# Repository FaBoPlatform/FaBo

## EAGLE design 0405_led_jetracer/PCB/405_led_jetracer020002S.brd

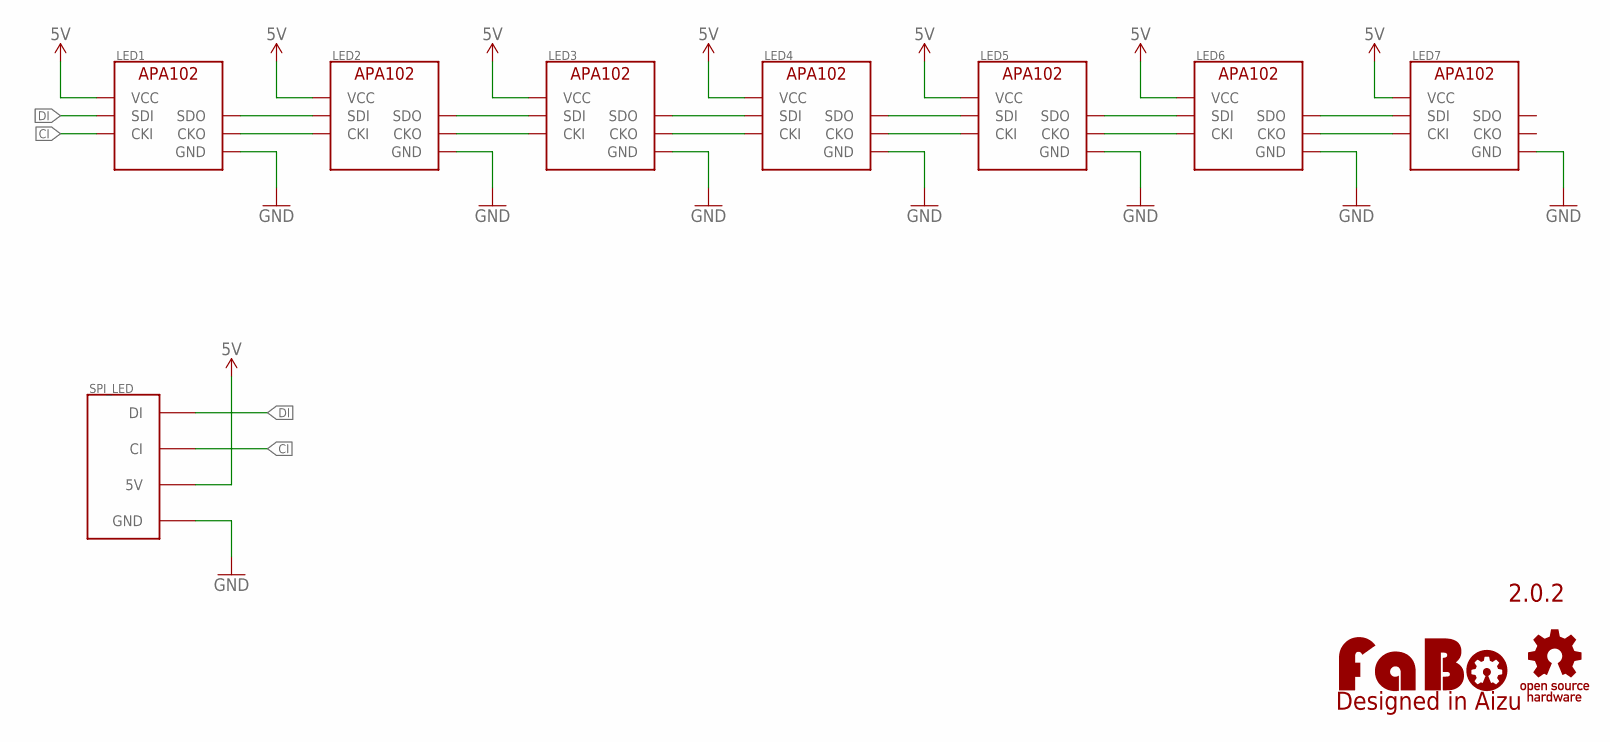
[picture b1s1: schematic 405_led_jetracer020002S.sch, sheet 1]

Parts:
LED1, LED2, LED3, LED4, LED5, LED6, LED7: APA102_IPIXEL; APA102_2020
LOGO1: LOGO_OSHW-S_BOTTOM; LOGO_OSHW_S_BOTTOM
LOGO2: LOGO_FABO-S; LOGO_FABO_S
SPI_LED: SPI-LED; FABO_BRICK_SPI_LED_S04B-PASK-2

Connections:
5V: LED1.VCC, LED2.VCC, LED3.VCC, LED4.VCC, LED5.VCC, LED6.VCC, LED7.VCC, SPI_LED.5V
CI: LED1.CKI, SPI_LED.CI
CI1: LED1.CKO, LED2.CKI
CI2: LED2.CKO, LED3.CKI
CI3: LED3.CKO, LED4.CKI
CI4: LED4.CKO, LED5.CKI
CI5: LED5.CKO, LED6.CKI
DI: LED1.SDI, SPI_LED.DI
DI1: LED1.SDO, LED2.SDI
DI2: LED2.SDO, LED3.SDI
DI3: LED3.SDO, LED4.SDI
DI4: LED4.SDO, LED5.SDI
DI5: LED5.SDO, LED6.SDI
GND: LED1.GND, LED2.GND, LED3.GND, LED4.GND, LED5.GND, LED6.GND, LED7.GND, SPI_LED.GND
unnamed: LED6.SDO, LED7.SDI
unnamed: LED6.CKO, LED7.CKI

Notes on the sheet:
2.0.2

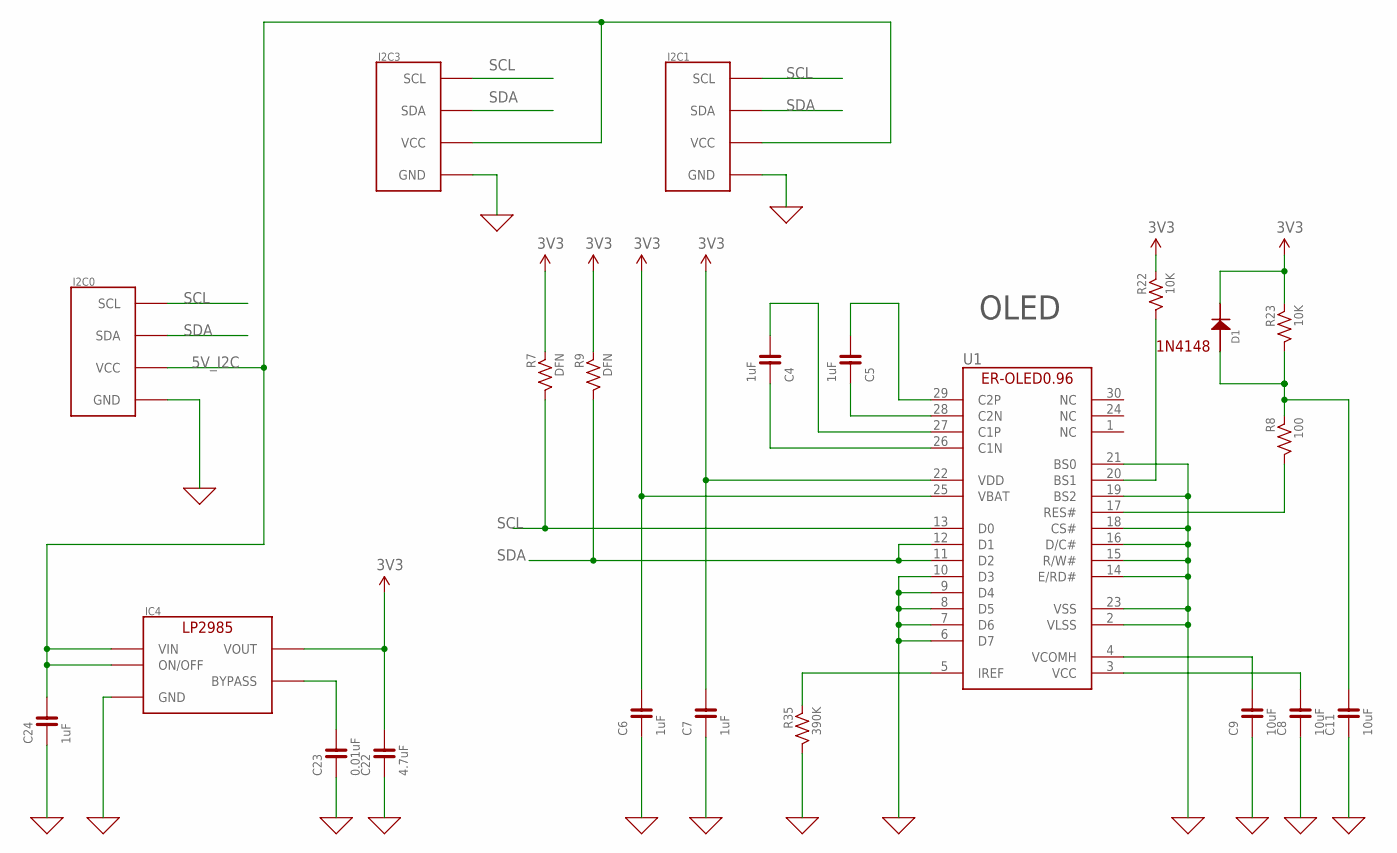
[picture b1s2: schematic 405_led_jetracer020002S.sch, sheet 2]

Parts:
C4, C5, C6, C7, C24: 1uF; 0603
C8, C9, C11: 10uF; 0603
C22: 4.7uF; 0603
C23: 0.01uF; 0603
D1: 1N4148; 1N4148W
I2C0, I2C1, I2C3: FABO_BRICK_I2C-S04B-PASK-2; FABO_BRICK_I2C_S04B-PASK-2
IC4: LP2985-33DBV; SOT-23-5
R7, R9: DFN; 0603
R8: 100; 0603
R22, R23: 10K; 0603
R35: 390K; 0603
U1: ER-OLED0.96-1ER-CON30HT-1; ER-CON30HT-1

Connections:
0: C6.1, C7.1, C8.1, C9.1, C11.1, C22.1, C23.1, C24.1, I2C0.GND, I2C1.GND, I2C3.GND, IC4.2 (GND), R35.2, U1.2 (VLSS), U1.6 (D7), U1.7 (D6), U1.8 (D5), U1.9 (D4), U1.10 (D3), U1.14 (E/RD#), U1.15 (R/W#), U1.16 (D/C#), U1.18 (CS#), U1.19 (BS2), U1.21 (BS0), U1.23 (VSS)
3V3: C6.2, C7.2, C22.2, D1.CATHODE, IC4.5 (VOUT), R7.1, R9.1, R22.1, R23.1, U1.22 (VDD), U1.25 (VBAT)
5V_I2C: C24.2, I2C0.VCC, I2C1.VCC, I2C3.VCC, IC4.1 (VIN), IC4.3 (ON/OFF)
unnamed: C23.2, IC4.4 (BYPASS)
unnamed: C4.2, U1.27 (C1P)
unnamed: C4.1, U1.26 (C1N)
unnamed: C5.1, U1.28 (C2N)
unnamed: C5.2, U1.29 (C2P)
unnamed: R35.1, U1.5 (IREF)
unnamed: C9.2, U1.4 (VCOMH)
unnamed: C8.2, U1.3 (VCC)
unnamed: R8.2, U1.17 (RES#)
unnamed: C11.2, D1.ANODE, R8.1, R23.2
unnamed: R22.2, U1.20 (BS1)
SCL: I2C0.SCL, I2C1.SCL, I2C3.SCL, R7.2, U1.13 (D0)
SDA: I2C0.SDA, I2C1.SDA, I2C3.SDA, R9.2, U1.11 (D2), U1.12 (D1)

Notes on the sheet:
1N4148
OLED

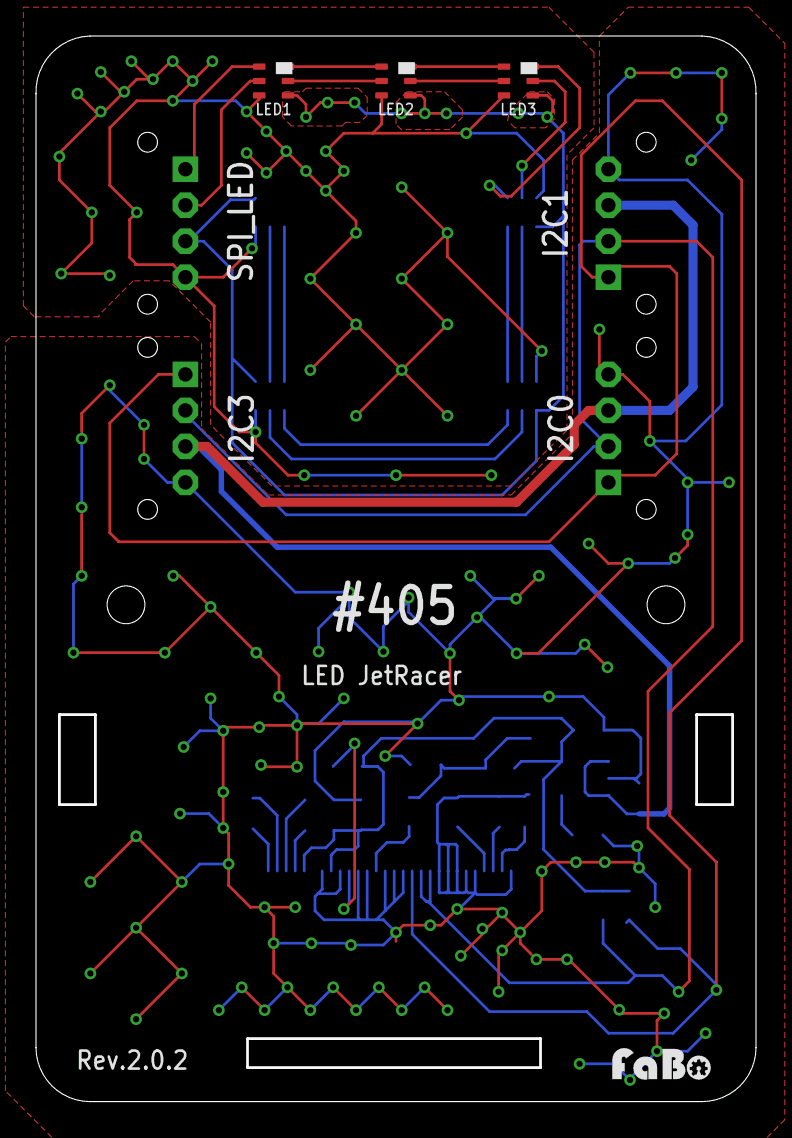
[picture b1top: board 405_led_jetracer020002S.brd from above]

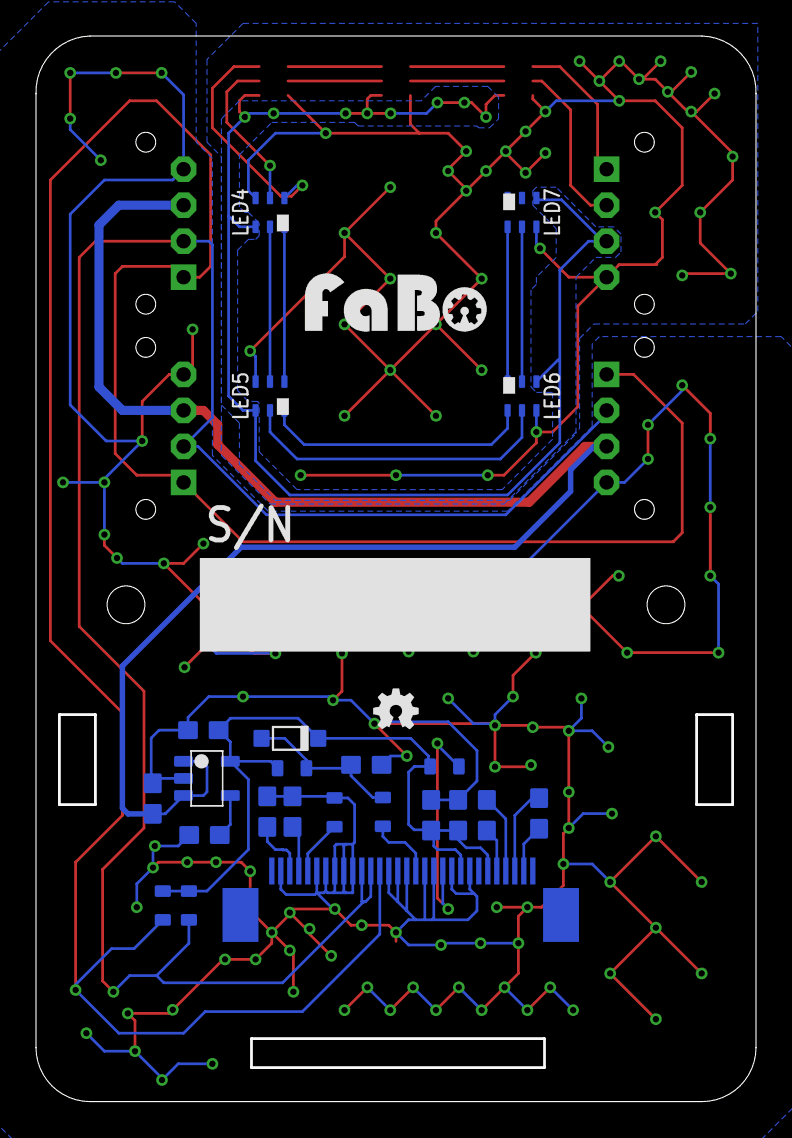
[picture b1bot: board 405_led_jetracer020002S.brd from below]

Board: 2 copper layers, 40.0 x 59.2 mm, 33 parts (22 on the bottom side), 32 nets.

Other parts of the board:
U$3: LOGO_FABO_M_BOTTOM

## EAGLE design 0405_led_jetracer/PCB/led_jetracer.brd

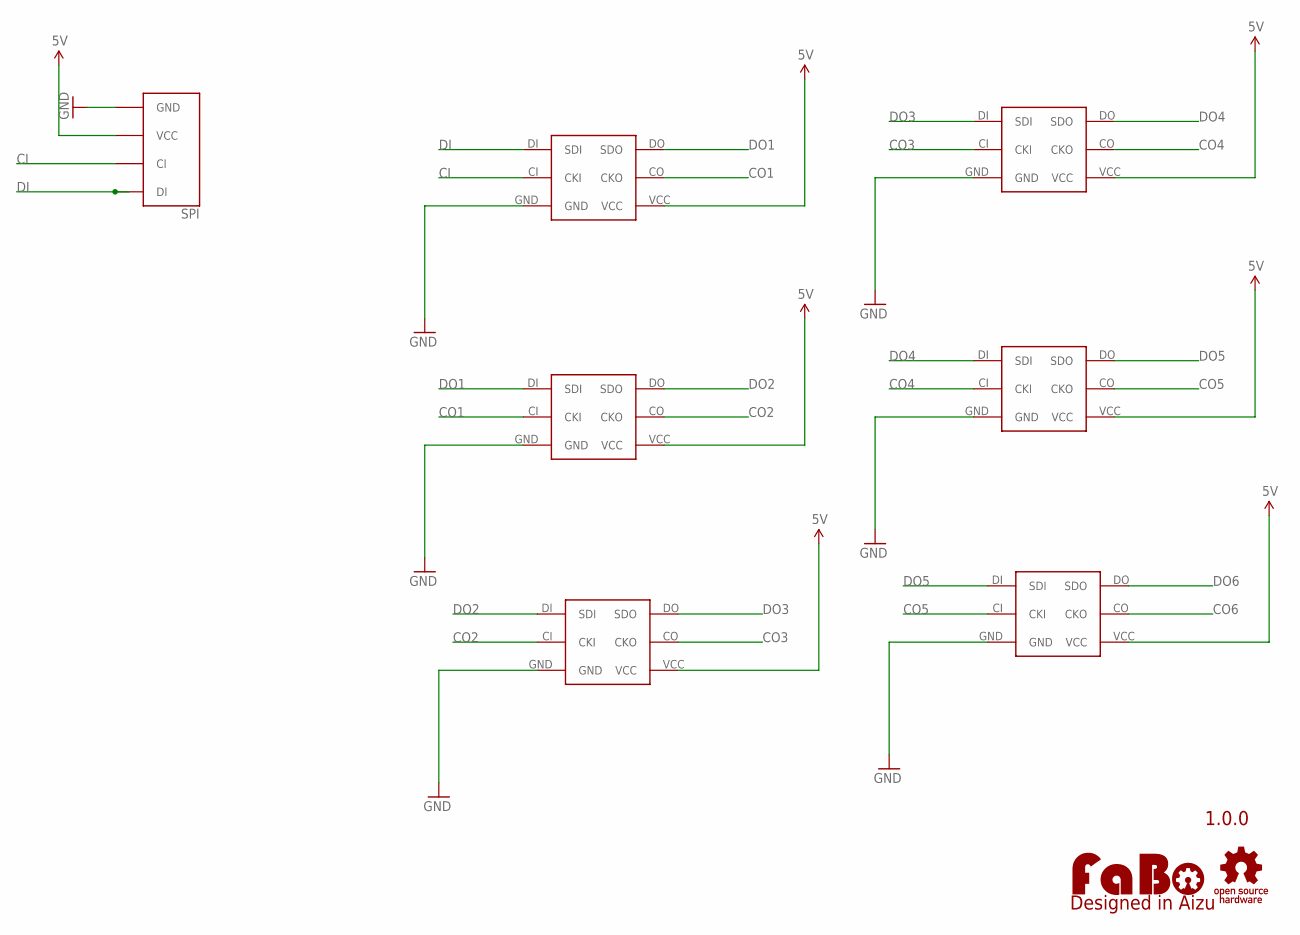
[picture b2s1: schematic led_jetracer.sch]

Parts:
LED0, LED1, LED2, LED3, LED4, LED5: APA102_IPIXEL; APA102(IPIXEL)
LOGO1: LOGO_FABO-S; LOGO_FABO_S
SPI: FABO-SPI-LED-B04B-BOTTOM; SPI-B04-PASK-1-BOTTOM
U$2: LOGO_OSHW-S_BOTTOM; LOGO_OSHW_S_BOTTOM

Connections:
5V: LED0.VCC, LED1.VCC, LED2.VCC, LED3.VCC, LED4.VCC, LED5.VCC, SPI.VCC
CI: LED0.CI (CKI), SPI.CI
CO1: LED0.CO (CKO), LED1.CI (CKI)
CO2: LED1.CO (CKO), LED2.CI (CKI)
CO3: LED2.CO (CKO), LED3.CI (CKI)
CO4: LED3.CO (CKO), LED4.CI (CKI)
CO5: LED4.CO (CKO), LED5.CI (CKI)
CO6: LED5.CO (CKO)
DI: LED0.DI (SDI), SPI.DI
DO1: LED0.DO (SDO), LED1.DI (SDI)
DO2: LED1.DO (SDO), LED2.DI (SDI)
DO3: LED2.DO (SDO), LED3.DI (SDI)
DO4: LED3.DO (SDO), LED4.DI (SDI)
DO5: LED4.DO (SDO), LED5.DI (SDI)
DO6: LED5.DO (SDO)
GND: LED0.GND, LED1.GND, LED2.GND, LED3.GND, LED4.GND, LED5.GND, SPI.GND

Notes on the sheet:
1.0.0

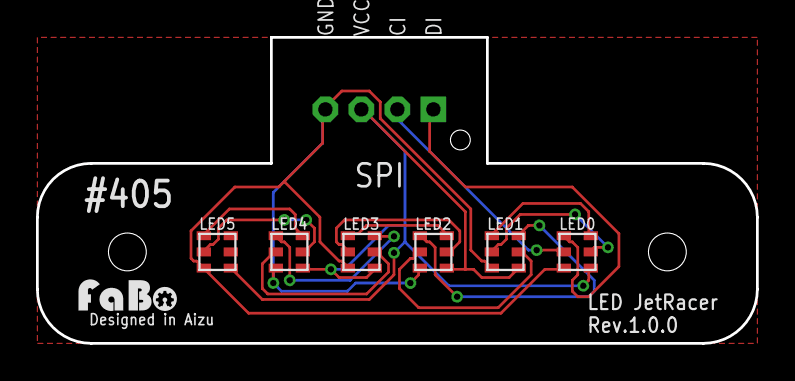
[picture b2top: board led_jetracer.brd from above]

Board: 2 copper layers, 40.0 x 17.0 mm, 9 parts (0 on the bottom side), 14 nets.

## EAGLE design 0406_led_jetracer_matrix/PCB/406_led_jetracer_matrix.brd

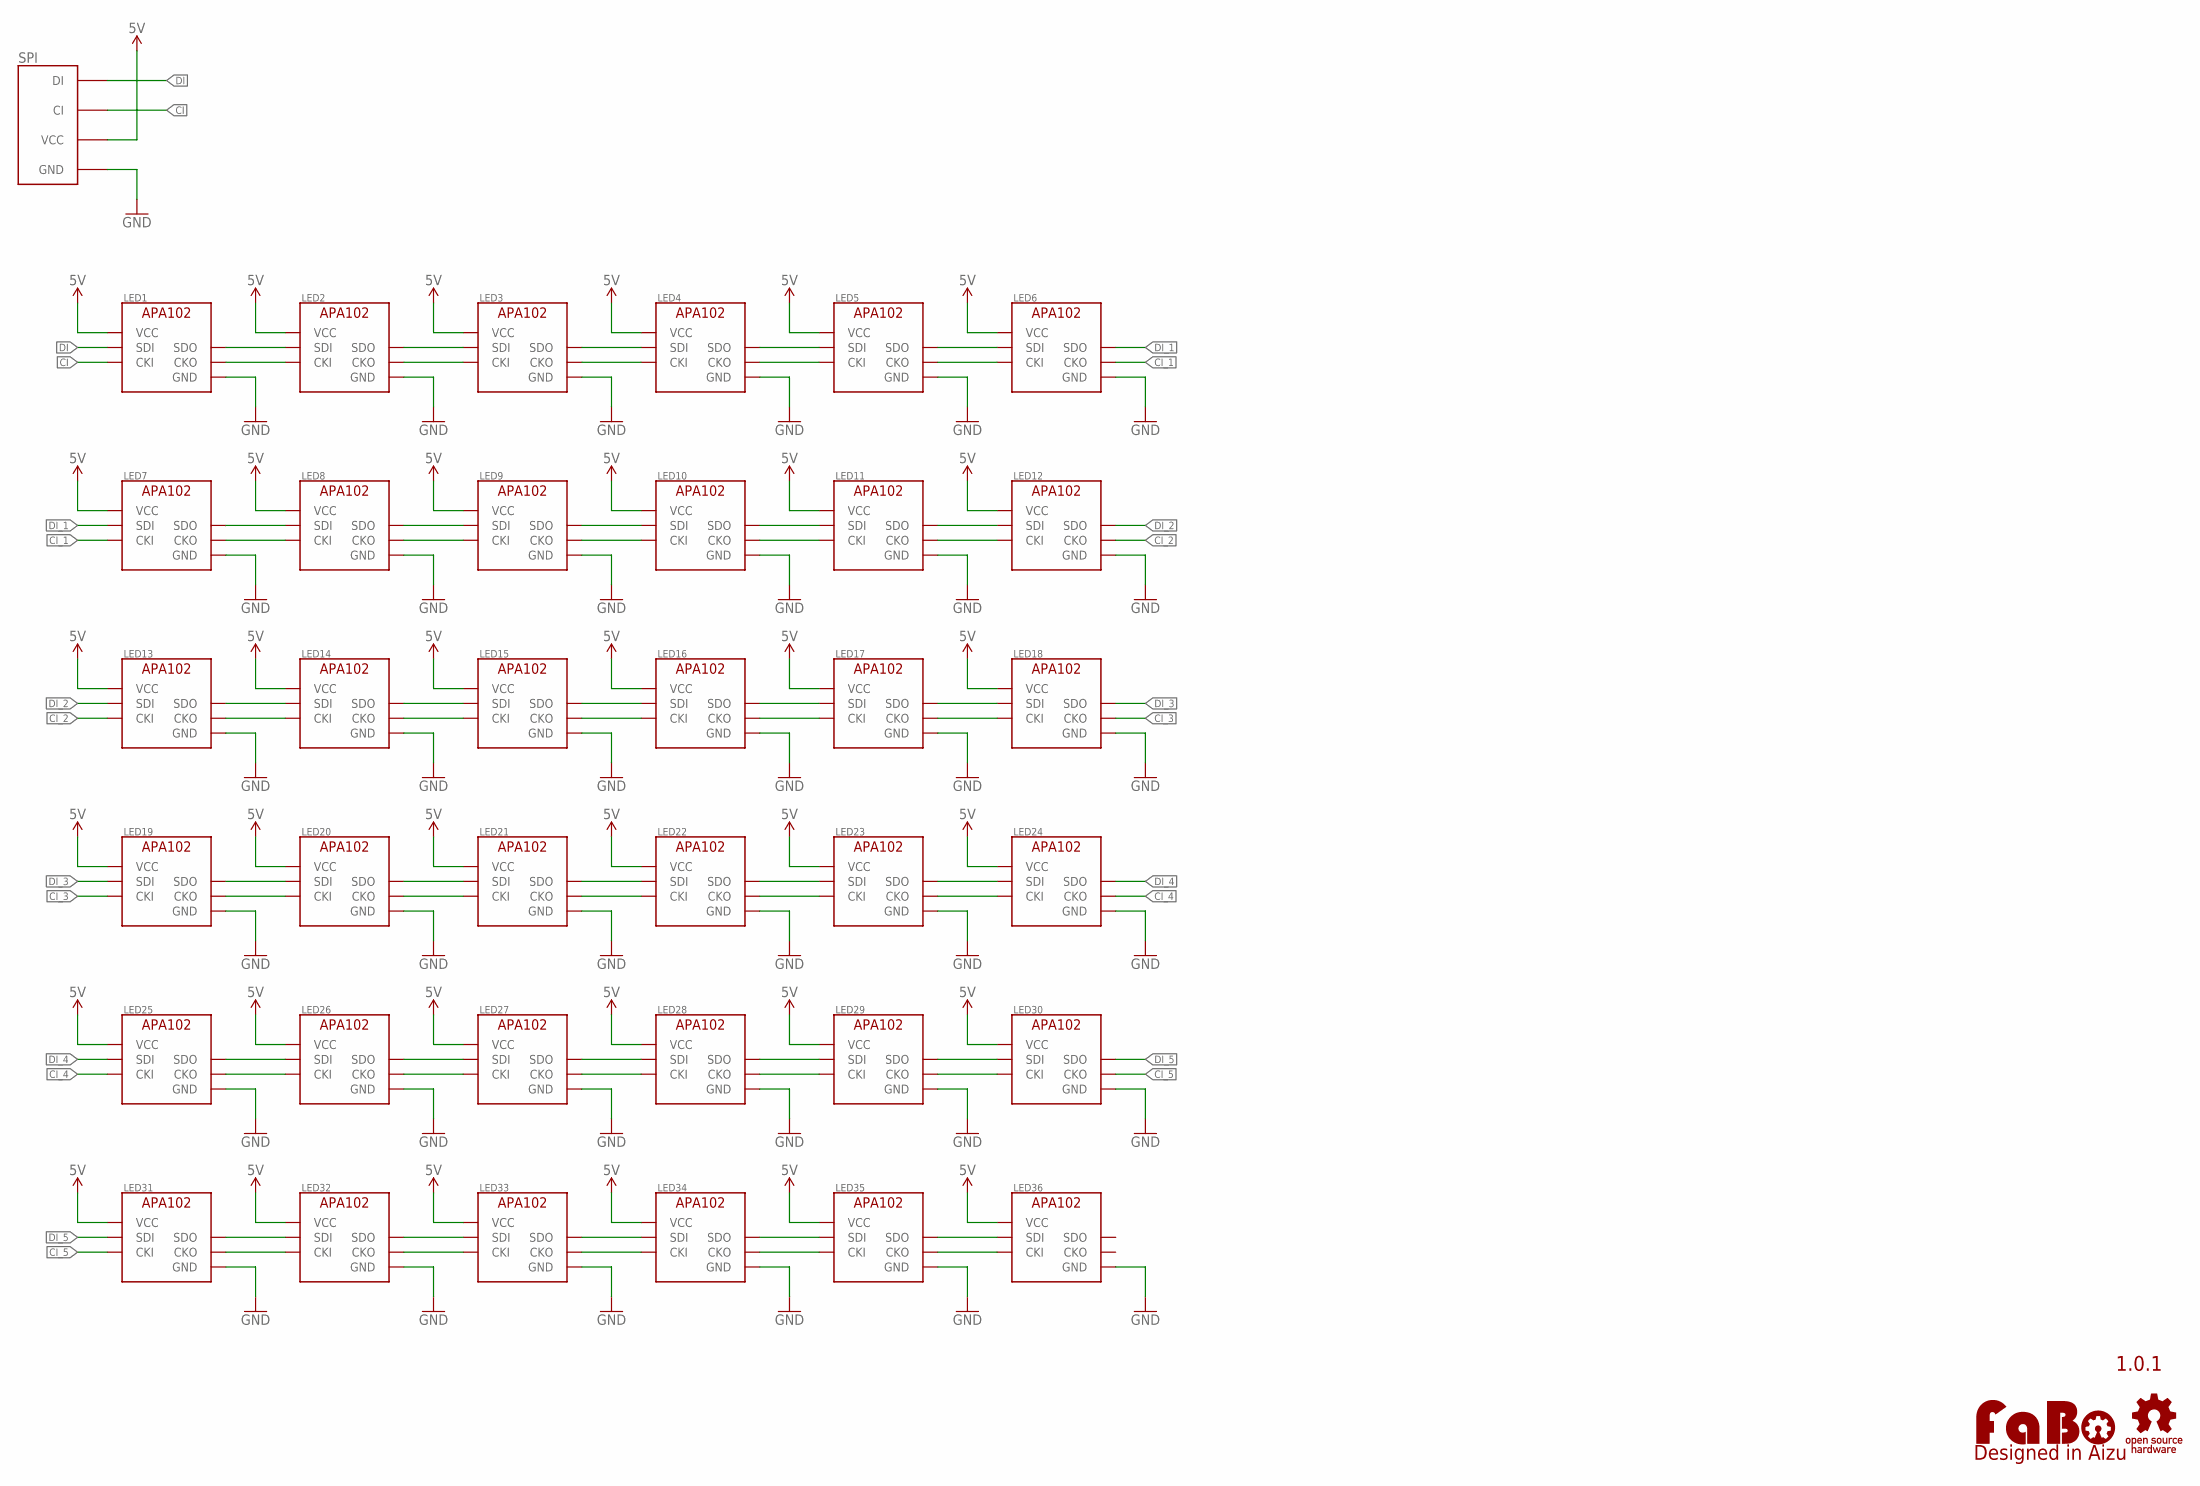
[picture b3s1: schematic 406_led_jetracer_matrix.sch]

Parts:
LED1, LED2, LED3, LED4, LED5, LED6, LED7, LED8, LED9, LED10, LED11, LED12, LED13, LED14, LED15, LED16, LED17, LED18, LED19, LED20, LED21, LED22, LED23, LED24, LED25, LED26, LED27, LED28, LED29, LED30, LED31, LED32, LED33, LED34, LED35, LED36: APA102_IPIXEL; APA102_2020
LOGO1: LOGO_OSHW-M_BOTTOM; LOGO_OSHW_M_BOTTOM
LOGO2: LOGO_FABO-M_BOTTOM; LOGO_FABO_M_BOTTOM
SPI: FABO-SPI-LED-B04B-BOTTOM; SPI-B04-PASK-1-BOTTOM

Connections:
5V: LED1.VCC, LED2.VCC, LED3.VCC, LED4.VCC, LED5.VCC, LED6.VCC, LED7.VCC, LED8.VCC, LED9.VCC, LED10.VCC, LED11.VCC, LED12.VCC, LED13.VCC, LED14.VCC, LED15.VCC, LED16.VCC, LED17.VCC, LED18.VCC, LED19.VCC, LED20.VCC, LED21.VCC, LED22.VCC, LED23.VCC, LED24.VCC, LED25.VCC, LED26.VCC, LED27.VCC, LED28.VCC, LED29.VCC, LED30.VCC, LED31.VCC, LED32.VCC, LED33.VCC, LED34.VCC, LED35.VCC, LED36.VCC, SPI.VCC
CI: LED1.CKI, SPI.CI
CI1: LED1.CKO, LED2.CKI
CI2: LED2.CKO, LED3.CKI
CI3: LED3.CKO, LED4.CKI
CI4: LED4.CKO, LED5.CKI
CI5: LED5.CKO, LED6.CKI
CI6: LED11.CKO, LED12.CKI
CI7: LED10.CKO, LED11.CKI
CI8: LED9.CKO, LED10.CKI
CI9: LED8.CKO, LED9.CKI
CI10: LED7.CKO, LED8.CKI
CI11: LED17.CKO, LED18.CKI
CI12: LED16.CKO, LED17.CKI
CI13: LED15.CKO, LED16.CKI
CI14: LED14.CKO, LED15.CKI
CI15: LED13.CKO, LED14.CKI
CI16: LED23.CKO, LED24.CKI
CI17: LED22.CKO, LED23.CKI
CI18: LED21.CKO, LED22.CKI
CI19: LED20.CKO, LED21.CKI
CI20: LED19.CKO, LED20.CKI
CI21: LED29.CKO, LED30.CKI
CI22: LED28.CKO, LED29.CKI
CI23: LED27.CKO, LED28.CKI
CI24: LED26.CKO, LED27.CKI
CI25: LED25.CKO, LED26.CKI
CI26: LED35.CKO, LED36.CKI
CI27: LED34.CKO, LED35.CKI
CI28: LED33.CKO, LED34.CKI
CI29: LED32.CKO, LED33.CKI
CI30: LED31.CKO, LED32.CKI
CI_1: LED6.CKO, LED7.CKI
CI_2: LED12.CKO, LED13.CKI
CI_3: LED18.CKO, LED19.CKI
CI_4: LED24.CKO, LED25.CKI
CI_5: LED30.CKO, LED31.CKI
DI: LED1.SDI, SPI.DI
DI1: LED1.SDO, LED2.SDI
DI2: LED2.SDO, LED3.SDI
DI3: LED3.SDO, LED4.SDI
DI4: LED4.SDO, LED5.SDI
DI5: LED5.SDO, LED6.SDI
DI6: LED11.SDO, LED12.SDI
DI7: LED10.SDO, LED11.SDI
DI8: LED9.SDO, LED10.SDI
DI9: LED8.SDO, LED9.SDI
DI10: LED7.SDO, LED8.SDI
DI11: LED17.SDO, LED18.SDI
DI12: LED16.SDO, LED17.SDI
DI13: LED15.SDO, LED16.SDI
DI14: LED14.SDO, LED15.SDI
DI15: LED13.SDO, LED14.SDI
DI16: LED23.SDO, LED24.SDI
DI17: LED22.SDO, LED23.SDI
DI18: LED21.SDO, LED22.SDI
DI19: LED20.SDO, LED21.SDI
DI20: LED19.SDO, LED20.SDI
DI21: LED29.SDO, LED30.SDI
DI22: LED28.SDO, LED29.SDI
DI23: LED27.SDO, LED28.SDI
DI24: LED26.SDO, LED27.SDI
DI25: LED25.SDO, LED26.SDI
DI26: LED35.SDO, LED36.SDI
DI27: LED34.SDO, LED35.SDI
DI28: LED33.SDO, LED34.SDI
DI29: LED32.SDO, LED33.SDI
DI30: LED31.SDO, LED32.SDI
DI_1: LED6.SDO, LED7.SDI
DI_2: LED12.SDO, LED13.SDI
DI_3: LED18.SDO, LED19.SDI
DI_4: LED24.SDO, LED25.SDI
DI_5: LED30.SDO, LED31.SDI
GND: LED1.GND, LED2.GND, LED3.GND, LED4.GND, LED5.GND, LED6.GND, LED7.GND, LED8.GND, LED9.GND, LED10.GND, LED11.GND, LED12.GND, LED13.GND, LED14.GND, LED15.GND, LED16.GND, LED17.GND, LED18.GND, LED19.GND, LED20.GND, LED21.GND, LED22.GND, LED23.GND, LED24.GND, LED25.GND, LED26.GND, LED27.GND, LED28.GND, LED29.GND, LED30.GND, LED31.GND, LED32.GND, LED33.GND, LED34.GND, LED35.GND, LED36.GND, SPI.GND

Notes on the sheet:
1.0.1

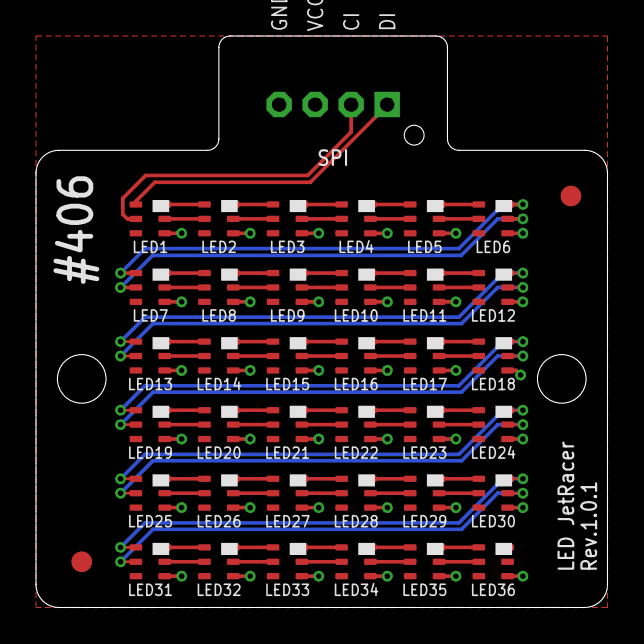
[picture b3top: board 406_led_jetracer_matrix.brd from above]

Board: 2 copper layers, 31.8 x 31.8 mm, 41 parts (0 on the bottom side), 74 nets.

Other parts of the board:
U$2, U$3: MARK_POINT_3MM

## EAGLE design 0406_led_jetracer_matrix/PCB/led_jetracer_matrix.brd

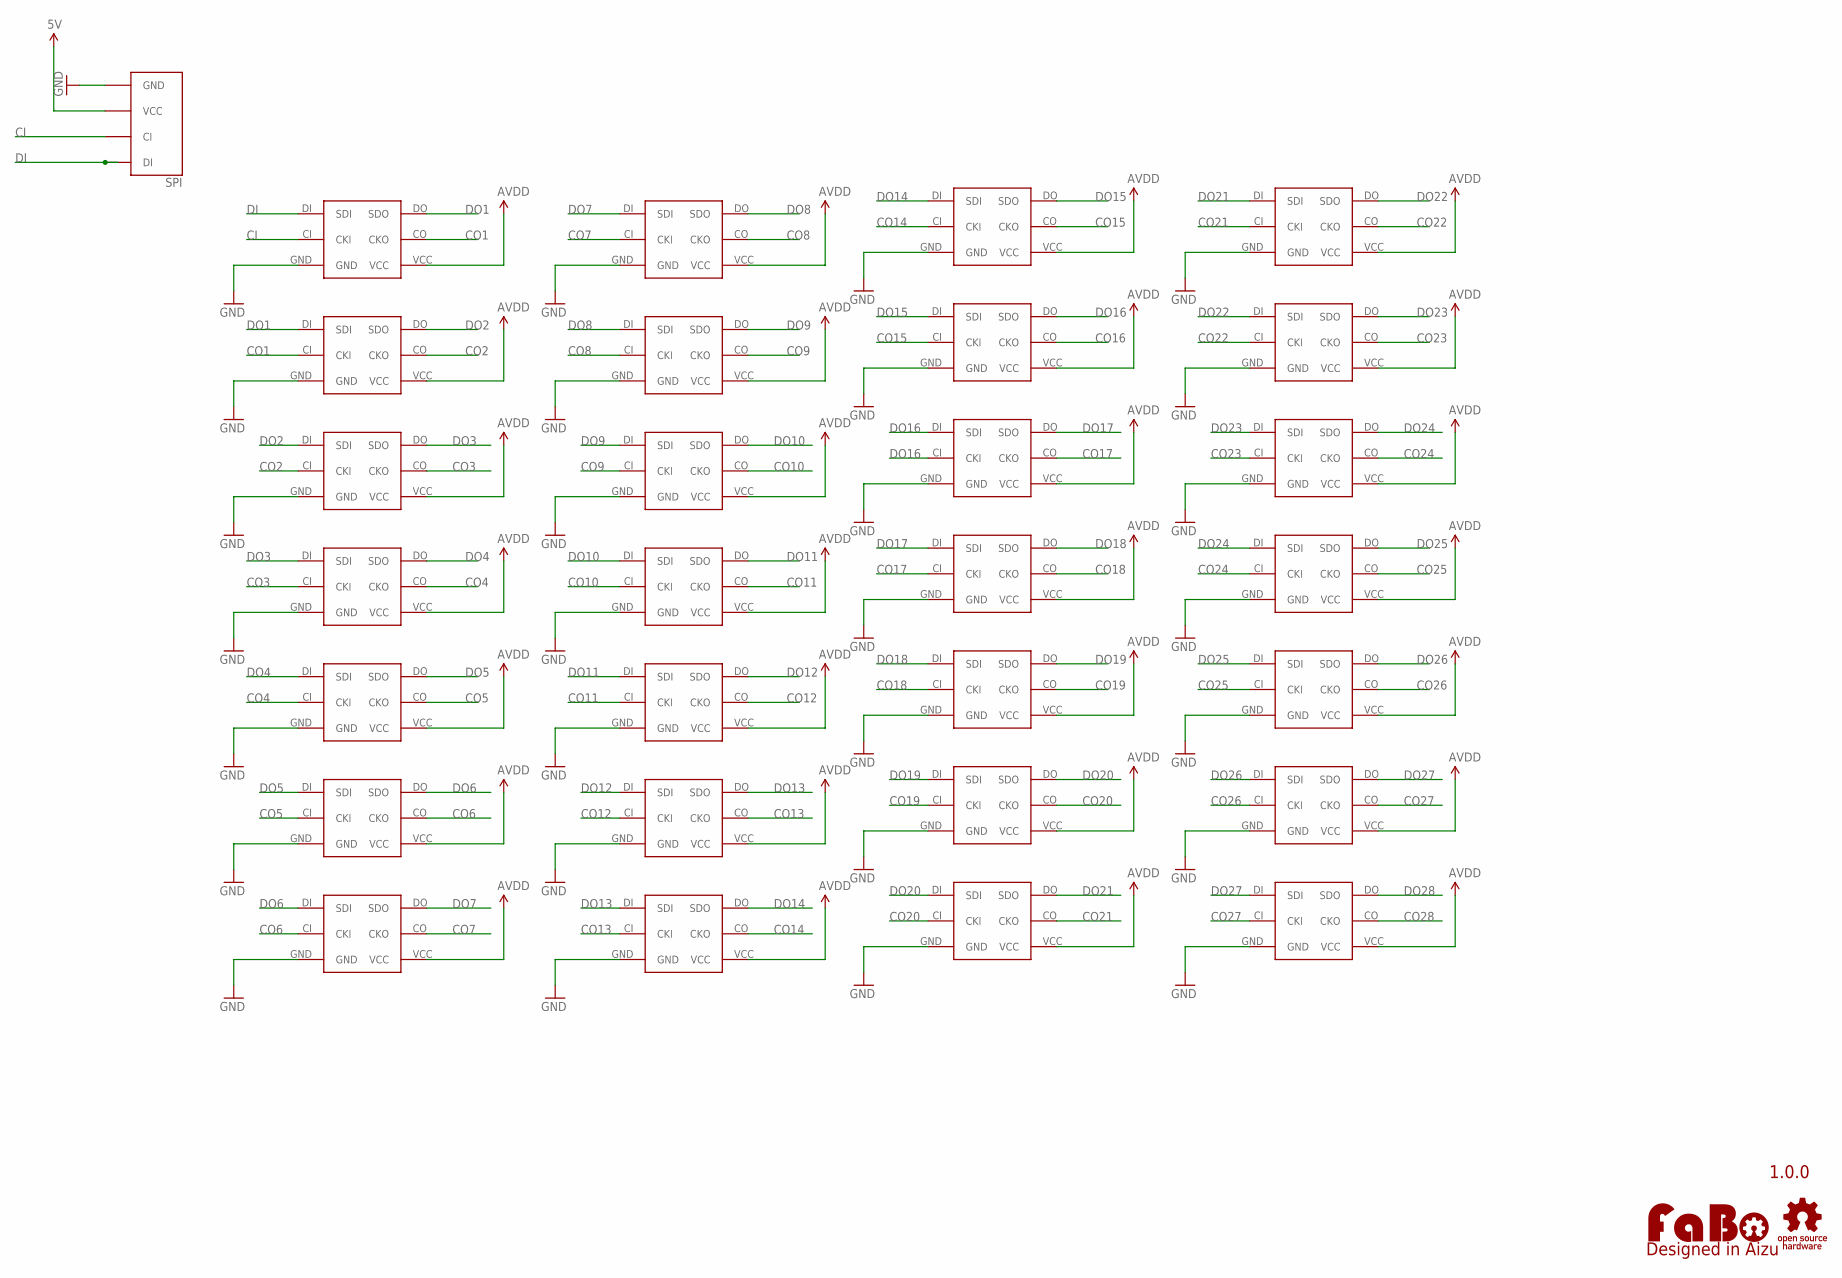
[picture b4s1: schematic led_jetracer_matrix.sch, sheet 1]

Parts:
0, 1, 2, 3, 4, 5, 6, 7, 8, 9, 10, 11, 12, 13, 14, 15, 16, 17, 18, 19, 20, 21, 22, 23, 24, 25, 26, 27: APA102_IPIXEL; APA102(IPIXEL)
LOGO1: LOGO_FABO-M_BOTTOM; LOGO_FABO_M_BOTTOM
SPI: FABO-SPI-LED-B04B-BOTTOM; SPI-B04-PASK-1-BOTTOM
U$3: LOGO_OSHW-S_BOTTOM; LOGO_OSHW_S_BOTTOM

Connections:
5V: SPI.VCC
AVDD: 0.VCC, 1.VCC, 2.VCC, 3.VCC, 4.VCC, 5.VCC, 6.VCC, 7.VCC, 8.VCC, 9.VCC, 10.VCC, 11.VCC, 12.VCC, 13.VCC, 14.VCC, 15.VCC, 16.VCC, 17.VCC, 18.VCC, 19.VCC, 20.VCC, 21.VCC, 22.VCC, 23.VCC, 24.VCC, 25.VCC, 26.VCC, 27.VCC; also elsewhere on the board
CI: 0.CI (CKI), SPI.CI
CO1: 0.CO (CKO), 1.CI (CKI)
CO2: 1.CO (CKO), 2.CI (CKI)
CO3: 2.CO (CKO), 3.CI (CKI)
CO4: 3.CO (CKO), 4.CI (CKI)
CO5: 4.CO (CKO), 5.CI (CKI)
CO6: 5.CO (CKO), 6.CI (CKI)
CO7: 6.CO (CKO), 7.CI (CKI)
CO8: 7.CO (CKO), 8.CI (CKI)
CO9: 8.CO (CKO), 9.CI (CKI)
CO10: 9.CO (CKO), 10.CI (CKI)
CO11: 10.CO (CKO), 11.CI (CKI)
CO12: 11.CO (CKO), 12.CI (CKI)
CO13: 12.CO (CKO), 13.CI (CKI)
CO14: 13.CO (CKO), 14.CI (CKI)
CO15: 14.CO (CKO), 15.CI (CKI)
CO16: 15.CO (CKO)
CO17: 16.CO (CKO), 17.CI (CKI)
CO18: 17.CO (CKO), 18.CI (CKI)
CO19: 18.CO (CKO), 19.CI (CKI)
CO20: 19.CO (CKO), 20.CI (CKI)
CO21: 20.CO (CKO), 21.CI (CKI)
CO22: 21.CO (CKO), 22.CI (CKI)
CO23: 22.CO (CKO), 23.CI (CKI)
CO24: 23.CO (CKO), 24.CI (CKI)
CO25: 24.CO (CKO), 25.CI (CKI)
CO26: 25.CO (CKO), 26.CI (CKI)
CO27: 26.CO (CKO), 27.CI (CKI)
CO28: 27.CO (CKO); also elsewhere on the board
DI: 0.DI (SDI), SPI.DI
DO1: 0.DO (SDO), 1.DI (SDI)
DO2: 1.DO (SDO), 2.DI (SDI)
DO3: 2.DO (SDO), 3.DI (SDI)
DO4: 3.DO (SDO), 4.DI (SDI)
DO5: 4.DO (SDO), 5.DI (SDI)
DO6: 5.DO (SDO), 6.DI (SDI)
DO7: 6.DO (SDO), 7.DI (SDI)
DO8: 7.DO (SDO), 8.DI (SDI)
DO9: 8.DO (SDO), 9.DI (SDI)
DO10: 9.DO (SDO), 10.DI (SDI)
DO11: 10.DO (SDO), 11.DI (SDI)
DO12: 11.DO (SDO), 12.DI (SDI)
DO13: 12.DO (SDO), 13.DI (SDI)
DO14: 13.DO (SDO), 14.DI (SDI)
DO15: 14.DO (SDO), 15.DI (SDI)
DO16: 15.DO (SDO), 16.CI (CKI), 16.DI (SDI)
DO17: 16.DO (SDO), 17.DI (SDI)
DO18: 17.DO (SDO), 18.DI (SDI)
DO19: 18.DO (SDO), 19.DI (SDI)
DO20: 19.DO (SDO), 20.DI (SDI)
DO21: 20.DO (SDO), 21.DI (SDI)
DO22: 21.DO (SDO), 22.DI (SDI)
DO23: 22.DO (SDO), 23.DI (SDI)
DO24: 23.DO (SDO), 24.DI (SDI)
DO25: 24.DO (SDO), 25.DI (SDI)
DO26: 25.DO (SDO), 26.DI (SDI)
DO27: 26.DO (SDO), 27.DI (SDI)
DO28: 27.DO (SDO); also elsewhere on the board
GND: 0.GND, 1.GND, 2.GND, 3.GND, 4.GND, 5.GND, 6.GND, 7.GND, 8.GND, 9.GND, 10.GND, 11.GND, 12.GND, 13.GND, 14.GND, 15.GND, 16.GND, 17.GND, 18.GND, 19.GND, 20.GND, 21.GND, 22.GND, 23.GND, 24.GND, 25.GND, 26.GND, 27.GND, SPI.GND; also elsewhere on the board

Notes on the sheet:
1.0.0

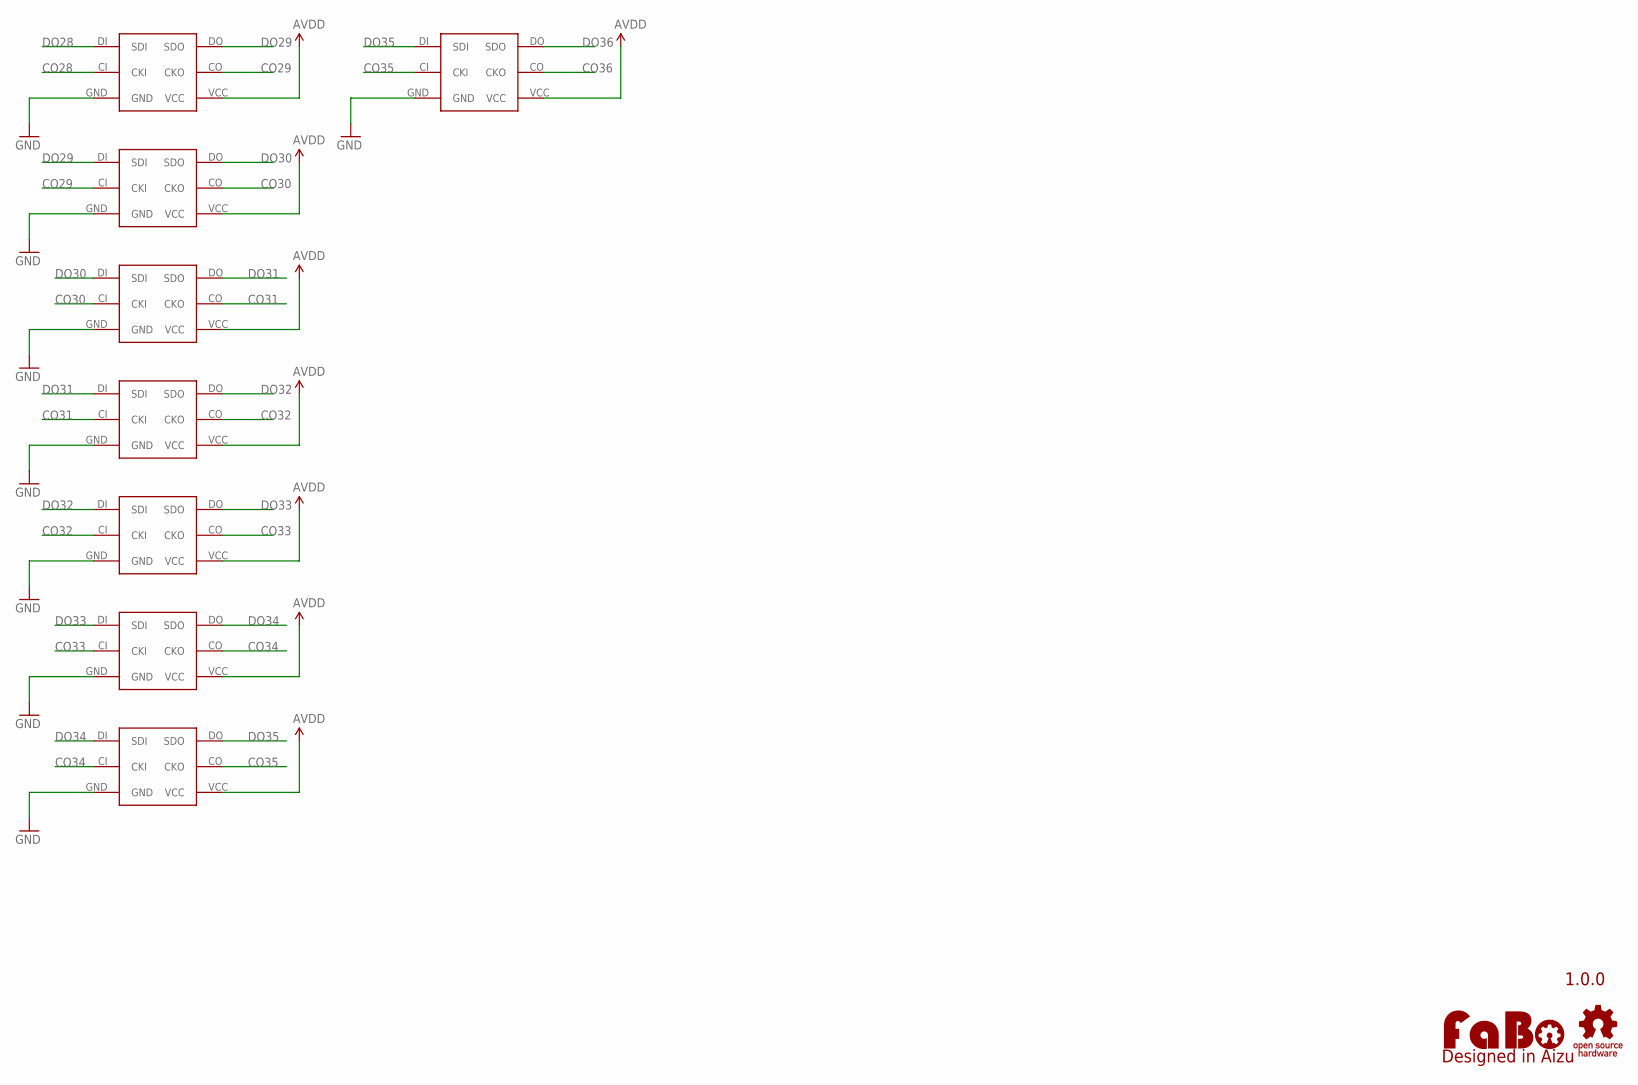
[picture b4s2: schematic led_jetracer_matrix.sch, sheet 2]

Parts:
28, 29, 30, 31, 32, 33, 34, 35: APA102_IPIXEL; APA102(IPIXEL)

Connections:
AVDD: 28.VCC, 29.VCC, 30.VCC, 31.VCC, 32.VCC, 33.VCC, 34.VCC, 35.VCC; also elsewhere on the board
CO28: 28.CI (CKI); also elsewhere on the board
CO29: 28.CO (CKO), 29.CI (CKI)
CO30: 29.CO (CKO), 30.CI (CKI)
CO31: 30.CO (CKO), 31.CI (CKI)
CO32: 31.CO (CKO), 32.CI (CKI)
CO33: 32.CO (CKO), 33.CI (CKI)
CO34: 33.CO (CKO), 34.CI (CKI)
CO35: 34.CO (CKO), 35.CI (CKI)
CO36: 35.CO (CKO)
DO28: 28.DI (SDI); also elsewhere on the board
DO29: 28.DO (SDO), 29.DI (SDI)
DO30: 29.DO (SDO), 30.DI (SDI)
DO31: 30.DO (SDO), 31.DI (SDI)
DO32: 31.DO (SDO), 32.DI (SDI)
DO33: 32.DO (SDO), 33.DI (SDI)
DO34: 33.DO (SDO), 34.DI (SDI)
DO35: 34.DO (SDO), 35.DI (SDI)
DO36: 35.DO (SDO)
GND: 28.GND, 29.GND, 30.GND, 31.GND, 32.GND, 33.GND, 34.GND, 35.GND; also elsewhere on the board

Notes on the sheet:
1.0.0

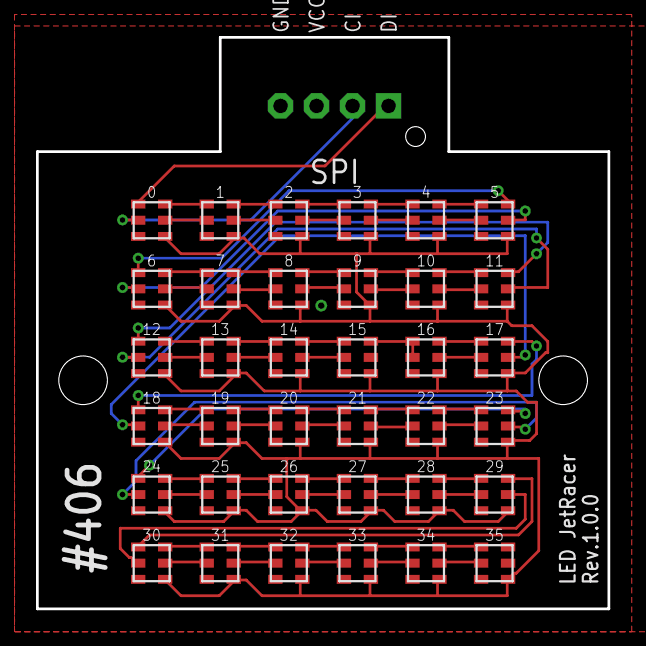
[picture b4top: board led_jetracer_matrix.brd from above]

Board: 2 copper layers, 31.8 x 31.8 mm, 39 parts (0 on the bottom side), 73 nets.

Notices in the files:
parts and their libraries:
FaBo-Logo: Released under the Creative Commons Attribution-ShareAlike 4.0 License
https://creativecommons.org/licenses/by-sa/4.0
FaBo-Symbol: Released under the Creative Commons
